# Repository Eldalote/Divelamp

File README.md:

# Divelamp
Designing my own dive lamp

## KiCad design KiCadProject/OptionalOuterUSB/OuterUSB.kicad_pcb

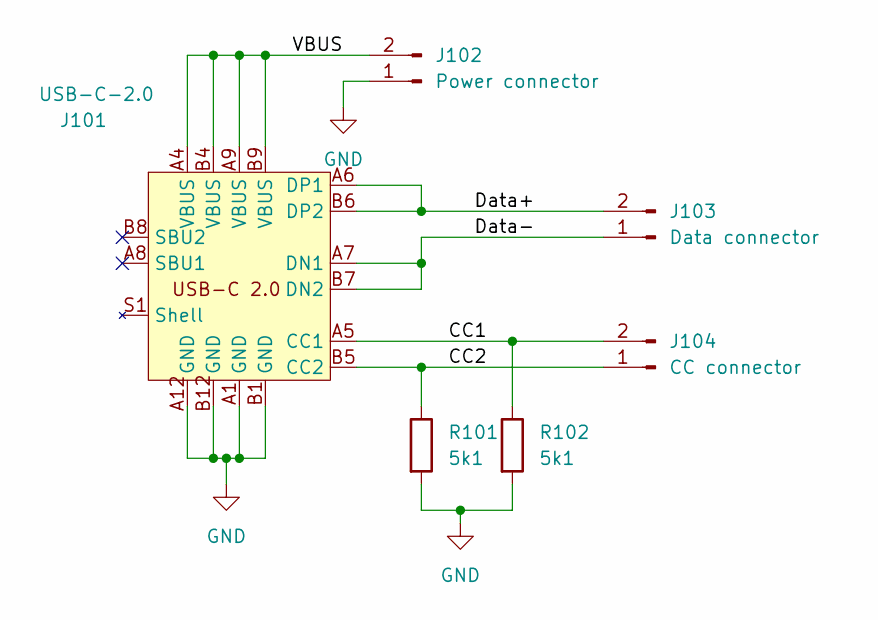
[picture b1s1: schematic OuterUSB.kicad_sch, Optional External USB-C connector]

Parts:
J101: USB-C-2.0; MOLEX_2130830005
J102: Power connector; PinHeader_1x02_P2.54mm_Vertical
J103: Data connector; PinHeader_1x02_P1.27mm_Vertical
J104: CC connector; PinHeader_1x02_P1.27mm_Vertical
R101, R102: 5k1; R_0402_1005Metric

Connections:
/CC1: J101.A5 (CC1), J104.2, R102.1
/CC2: J101.B5 (CC2), J104.1, R101.1
/Data+: J101.A6 (DP1), J101.B6 (DP2), J103.2
/Data-: J101.A7 (DN1), J101.B7 (DN2), J103.1
/VBUS: J101.A4 (VBUS), J101.A9 (VBUS), J101.B4 (VBUS), J101.B9 (VBUS), J102.2
GND: J101.A1 (GND), J101.A12 (GND), J101.B1 (GND), J101.B12 (GND), J102.1, R101.2, R102.2

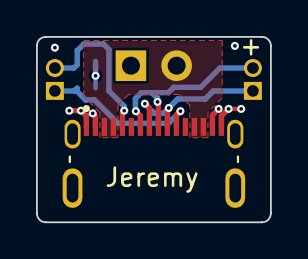
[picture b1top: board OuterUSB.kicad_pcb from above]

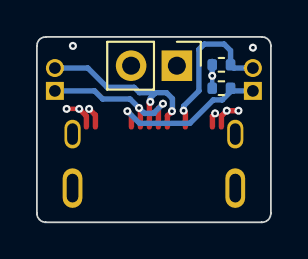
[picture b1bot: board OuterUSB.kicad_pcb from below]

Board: 4 copper layers, 13.0 x 10.3 mm, 6 parts (4 on the bottom side), 6 nets.

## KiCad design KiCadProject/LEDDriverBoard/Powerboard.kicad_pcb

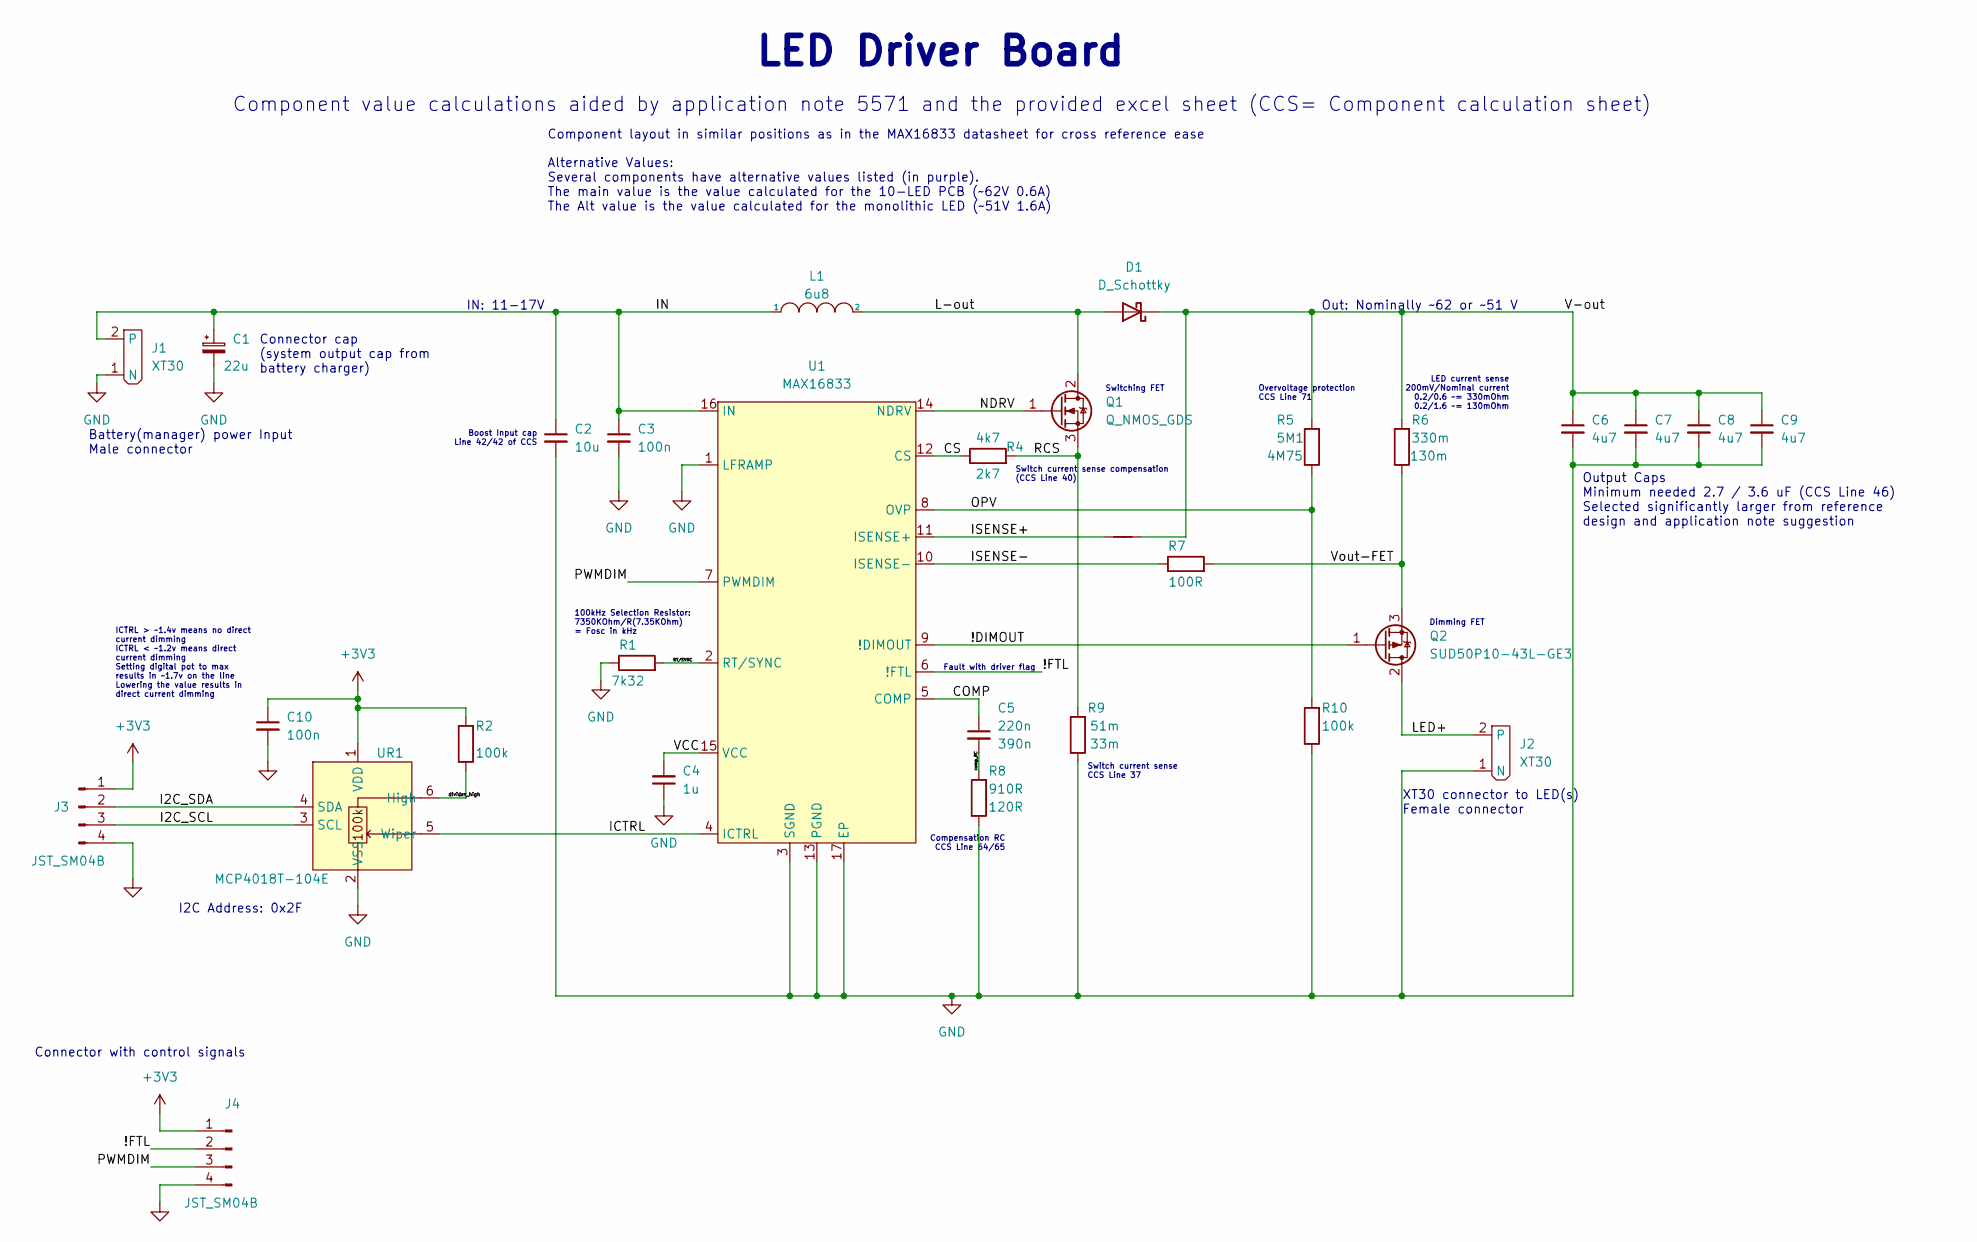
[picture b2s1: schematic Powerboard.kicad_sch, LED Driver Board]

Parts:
C1: 22u; CP_Elec_5x5.3
C2: 10u; C_1206_3216Metric
C3: 100n; C_0603_1608Metric
C4: 1u; C_0402_1005Metric
C5: 220n; C_0603_1608Metric
C6, C7, C8, C9: 4u7; C_1206_3216Metric
C10: 100n; C_0402_1005Metric
D1: D_Schottky; D_PowerDI-5
J1: XT30
J2: XT30; XT30_Female
J3, J4: JST_SM04B; JST_SH_SM04B-SRSS-TB_1x04-1MP_P1.00mm_Horizontal
L1: 6u8; SRP-1265C
NT1: NetTie_2; NetTie-2_SMD_Pad0.5mm
Q1: Q_NMOS_GDS; TO-252-2
Q2: SUD50P10-43L-GE3; TO-252-2
R1: 7k32; R_0402_1005Metric
R2, R10: 100k; R_0402_1005Metric
R4: 4k7; R_0402_1005Metric
R5: 5M1; R_0603_1608Metric
R6: 330m; R_1206_3216Metric
R7: 100R; R_0805_2012Metric
R8: 910R; R_0402_1005Metric
R9: 51m; R_1206_3216Metric
U1: MAX16833; HTSSOP-16-1EP_4.4x5mm_P0.65mm_EP3.4x5mm_Mask2.46x2.31mm_The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
UR1: MCP4018T-104E; SOT-363_SC-70-6

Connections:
+3V3: C10.1, J3.1, J4.1, R2.2, UR1.1 (VDD)
/!DIMOUT: Q2.1 (G), U1.9 (!DIMOUT)
/!FTL: J4.2, U1.6 (!FTL)
/COMP: C5.1, U1.5 (COMP)
/CS: R4.1, U1.12 (CS)
/I2C_SCL: J3.3, UR1.3 (SCL)
/I2C_SDA: J3.2, UR1.4 (SDA)
/ICTRL: U1.4 (ICTRL), UR1.5 (Wiper)
/IN: C1.1, C2.1, C3.1, J1.2, L1.1, U1.16 (IN)
/ISENSE+: NT1.1, U1.11 (ISENSE+)
/ISENSE-: R7.1, U1.10 (ISENSE-)
/L-out: D1.2 (A), L1.2, Q1.2 (D)
/LED+: J2.2, Q2.2 (D)
/NDRV: Q1.1 (G), U1.14 (NDRV)
/OPV: R5.1, R10.2, U1.8 (OVP)
/PWMDIM: J4.3, U1.7 (PWMDIM)
/RCS: Q1.3 (S), R4.2, R9.2
/RT/SYNC: R1.2, U1.2 (RT/SYNC)
/V-out: C6.1, C7.1, C8.1, C9.1, D1.1 (K), NT1.2, R5.2, R6.2
/VCC: C4.2, U1.15 (VCC)
/Vout-FET: Q2.3 (S), R6.1, R7.2
/comp_RC: C5.2, R8.2
/divider_high: R2.1, UR1.6 (High)
GND: C1.2, C2.2, C3.2, C4.1, C6.2, C7.2, C8.2, C9.2, C10.2, J1.1 (N), J2.1 (N), J3.4, J4.4, R1.1, R8.1, R9.1, R10.1, U1.1 (LFRAMP), U1.3 (SGND), U1.13 (PGND), U1.17 (EP), UR1.2 (VSS)

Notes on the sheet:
Switch current sense CCS Line 37
Connector cap (system output cap from battery charger)
ICTRL > ~1.4v means no direct current dimming ICTRL < ~1.2v means direct current dimming Setting digital pot to max results in ~1.7v on the line Lowering the value results in direct current dimming
LED current sense 200mV/Nominal current 0.2/0.6 ~= 330mOhm 0.2/1.6 ~= 130mOhm
Compensation RC CCS Line 64/65
Dimming FET
Fault with driver flag
XT30 connector to LED(s) Female connector
Switch current sense compensation (CCS Line 40)
Out: Nominally ~62 or ~51 V
Connector with control signals
I2C Address: 0x2F
Switching FET
Overvoltage protection CCS Line 71
Output Caps Minimum needed 2.7 / 3.6 uF (CCS Line 46) Selected significantly larger from reference design and application note suggestion
LED Driver Board
Component value calculations aided by application note 5571 and the provided excel sheet (CCS= Component calculation sheet)
IN: 11-17V
Alternative Values: Several components have alternative values listed (in purple). The main value is the value calculated for the 10-LED PCB (~62V 0.6A) The Alt value is the value calculated for the monolithic LED (~51V 1.6A)
Boost Input cap Line 42/42 of CCS
Component layout in similar positions as in the MAX16833 datasheet for cross reference ease
100kHz Selection Resistor: 7350KOhm/R(7.35KOhm) = Fosc in kHz
Battery(manager) power Input Male connector

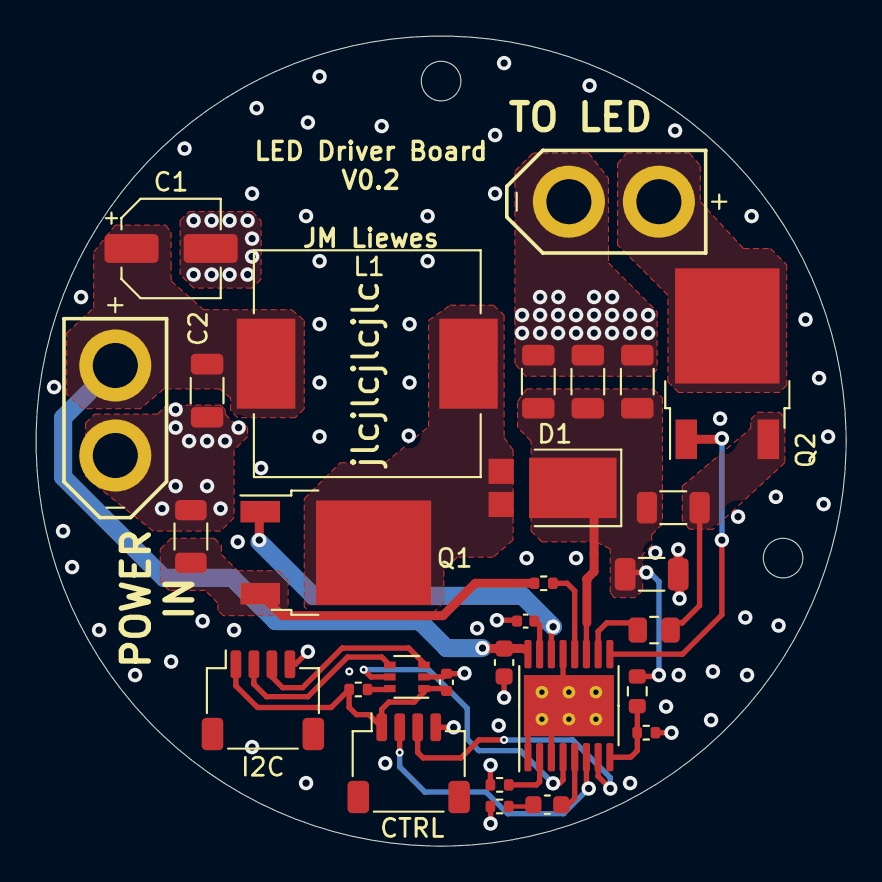
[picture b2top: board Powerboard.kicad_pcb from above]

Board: 4 copper layers, 45.0 x 45.0 mm, 30 parts (0 on the bottom side), 24 nets.

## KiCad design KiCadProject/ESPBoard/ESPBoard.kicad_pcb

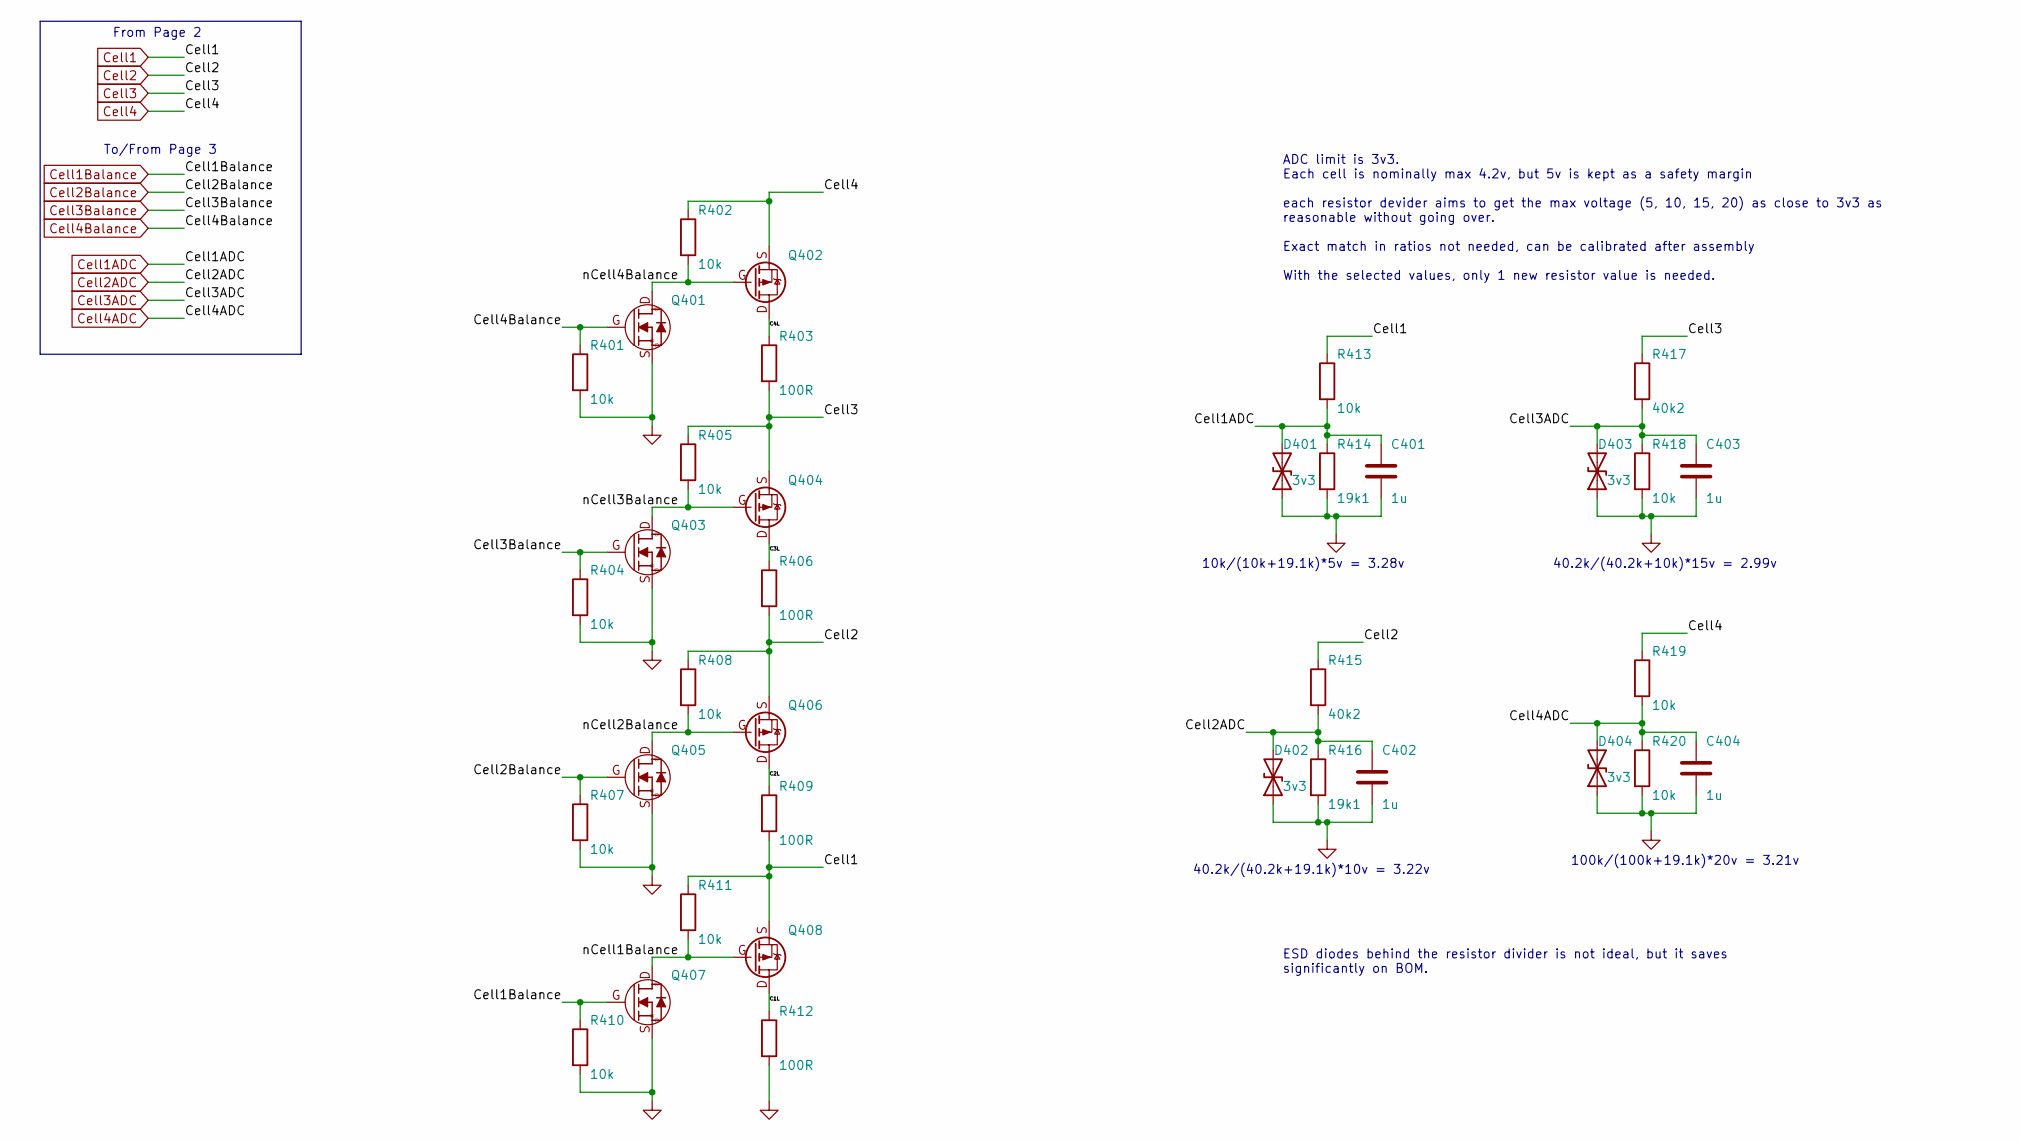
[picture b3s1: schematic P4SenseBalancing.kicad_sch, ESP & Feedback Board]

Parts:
C401, C402, C403, C404: 1u; C_0603_1608Metric
D401, D402, D403, D404: 3v3; D_SOD-523
Q401, Q403, Q405, Q407: NFET_Gatenames; SC-89(GSD)
Q402, Q404, Q406, Q408: PMOS_Gatenames; SOT-723(GSD)
R401, R402, R404, R405, R407, R408, R410, R411, R413, R418, R419, R420: 10k; R_0402_1005Metric
R403, R406, R409, R412: 100R; R_0805_2012Metric
R414, R416: 19k1; R_0402_1005Metric
R415, R417: 40k2; R_0402_1005Metric

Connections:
/P4 Batsense-Balancing/C1L: Q408.D, R412.1
/P4 Batsense-Balancing/C2L: Q406.D, R409.1
/P4 Batsense-Balancing/C3L: Q404.D, R406.1
/P4 Batsense-Balancing/C4L: Q402.D, R403.1
/P4 Batsense-Balancing/nCell1Balance: Q407.D, Q408.G, R411.2
/P4 Batsense-Balancing/nCell2Balance: Q405.D, Q406.G, R408.2
/P4 Batsense-Balancing/nCell3Balance: Q403.D, Q404.G, R405.2
/P4 Batsense-Balancing/nCell4Balance: Q401.D, Q402.G, R402.2
Cell1: Q408.S, R409.2, R411.1, R413.1; also elsewhere on the board
Cell1ADC: C401.1, D401.2 (A2), R413.2, R414.1; also elsewhere on the board
Cell1Balance: Q407.G, R410.1; also elsewhere on the board
Cell2: Q406.S, R406.2, R408.1, R415.1; also elsewhere on the board
Cell2ADC: C402.1, D402.2 (A2), R415.2, R416.1; also elsewhere on the board
Cell2Balance: Q405.G, R407.1; also elsewhere on the board
Cell3: Q404.S, R403.2, R405.1, R417.1; also elsewhere on the board
Cell3ADC: C403.1, D403.2 (A2), R417.2, R418.1; also elsewhere on the board
Cell3Balance: Q403.G, R404.1; also elsewhere on the board
Cell4: Q402.S, R402.1, R419.1; also elsewhere on the board
Cell4ADC: C404.1, D404.2 (A2), R419.2, R420.1; also elsewhere on the board
Cell4Balance: Q401.G, R401.1; also elsewhere on the board
GND: C401.2, C402.2, C403.2, C404.2, D401.1 (A1), D402.1 (A1), D403.1 (A1), D404.1 (A1), Q401.S, Q403.S, Q405.S, Q407.S, R401.2, R404.2, R407.2, R410.2, R412.2, R414.2, R416.2, R418.2, R420.2; also elsewhere on the board

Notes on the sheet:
10k/(10k+19.1k)*5v = 3.28v
40.2k/(40.2k+10k)*15v = 2.99v
40.2k/(40.2k+19.1k)*10v = 3.22v
100k/(100k+19.1k)*20v = 3.21v
ADC limit is 3v3. Each cell is nominally max 4.2v, but 5v is kept as a safety margin each resistor devider aims to get the max voltage (5, 10, 15, 20) as close to 3v3 as reasonable without going over. Exact match in ratios not needed, can be calibrated after assembly With the selected values, only 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
From Page 2
ESD diodes behind the resistor divider is not ideal, but it saves significantly on BOM.
To/From Page 3

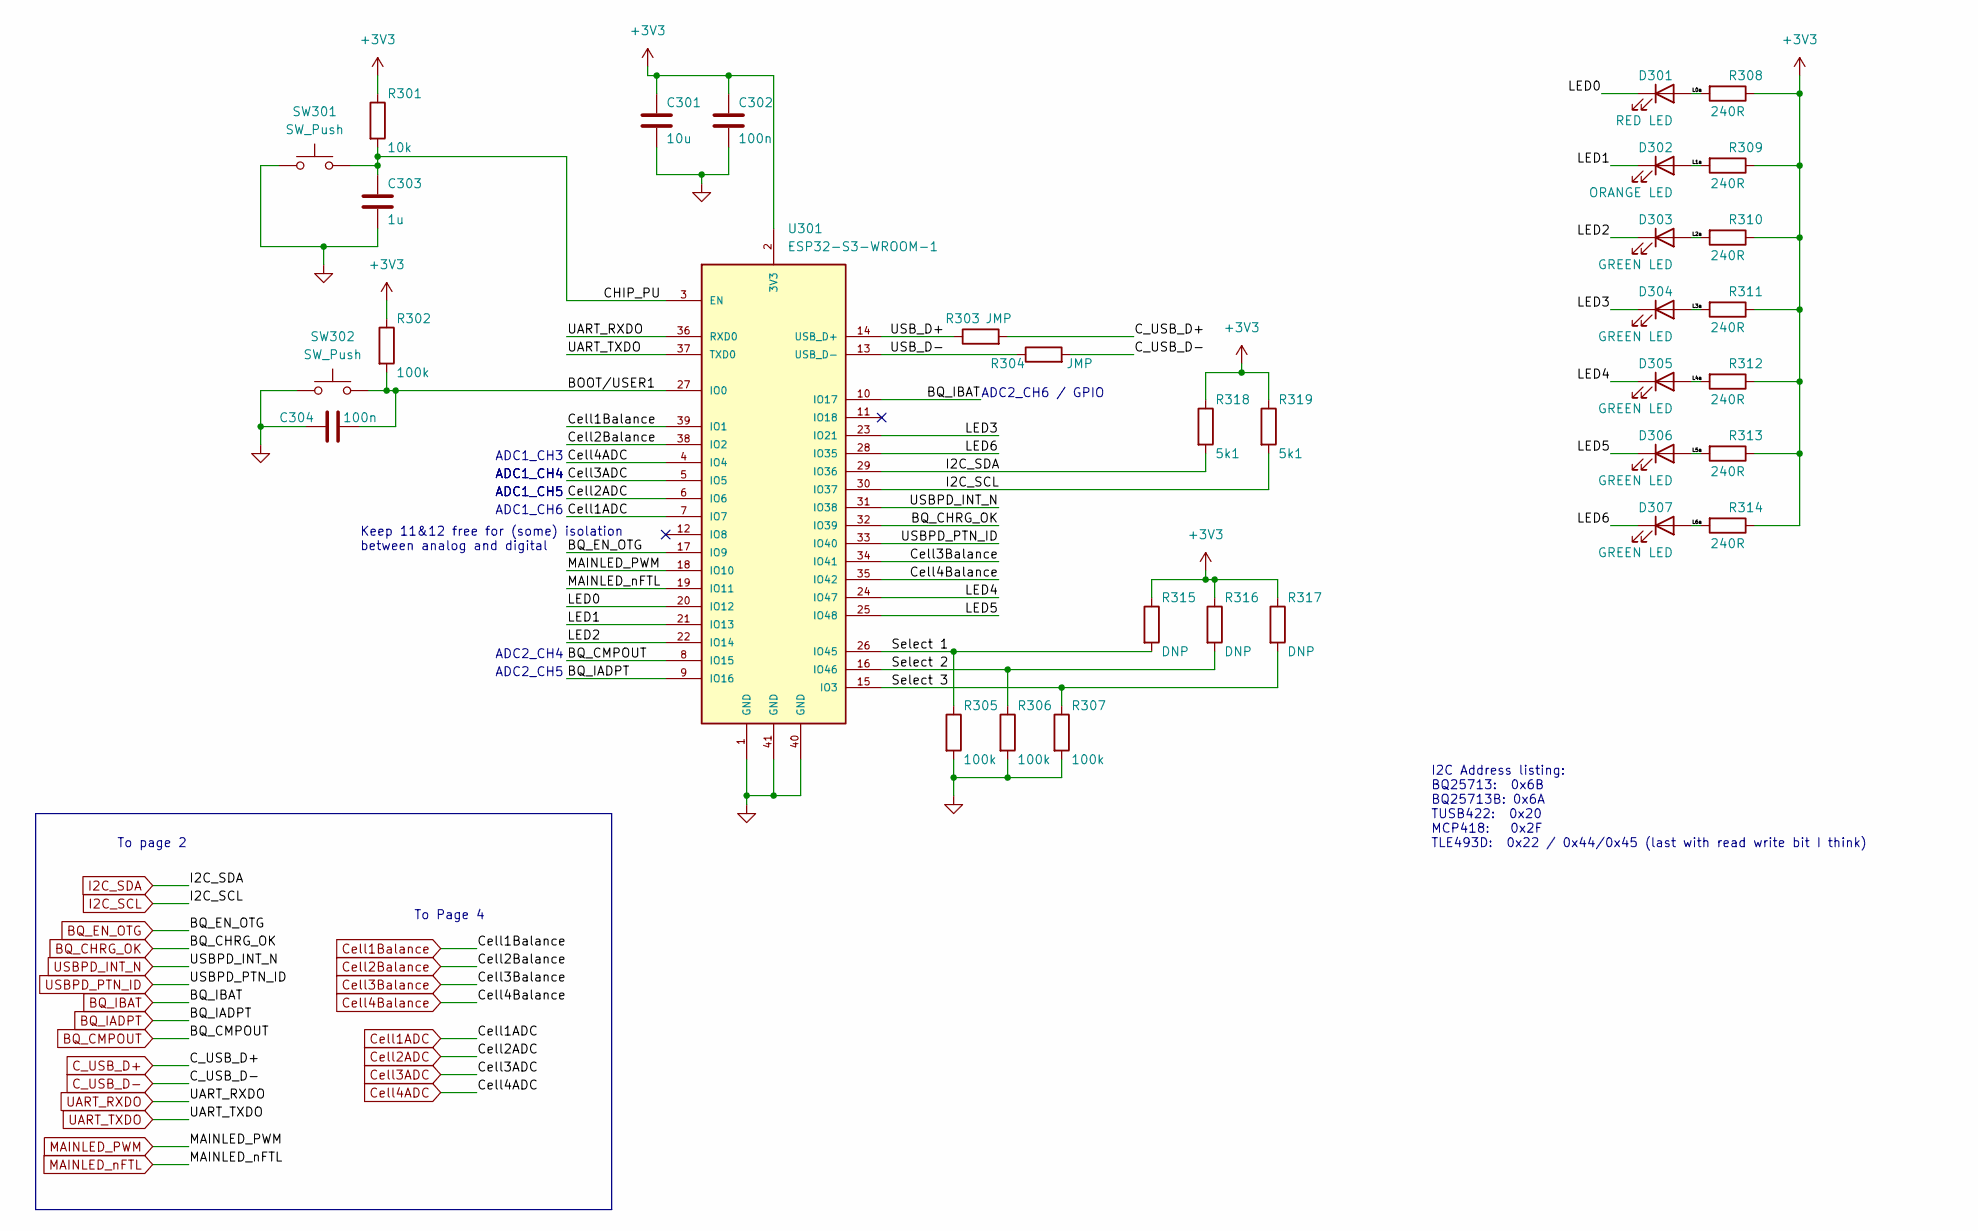
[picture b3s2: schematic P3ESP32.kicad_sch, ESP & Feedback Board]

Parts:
C301: 10u; C_0805_2012Metric
C302, C304: 100n; C_0402_1005Metric
C303: 1u; C_0603_1608Metric
D301: RED LED; LED_0805_2012Metric
D302: ORANGE LED; LED_0805_2012Metric
D303, D304, D305, D306, D307: GREEN LED; LED_0805_2012Metric
R301: 10k; R_0402_1005Metric
R302, R305, R306, R307: 100k; R_0402_1005Metric
R303, R304: JMP; R_0402_1005Metric
R308, R309, R310, R311, R312, R313, R314: 240R; R_0402_1005Metric
R315, R316, R317: DNP; R_0402_1005Metric
R318, R319: 5k1; R_0402_1005Metric
SW301, SW302: SW_Push; SW_Push_1P1T_NO_6x6mm_H9.5mm
U301: ESP32-S3-WROOM-1; XCVR_ESP32-S3-WROOM-1

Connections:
+3V3: C301.1, C302.1, R301.1, R302.1, R308.1, R309.1, R310.1, R311.1, R312.1, R313.1, R314.1, R315.1, R316.1, R317.1, R318.1, R319.1, U301.2 (3V3); also elsewhere on the board
/P3 ESP32/BOOT/USER1: C304.2, R302.2, SW302.2, U301.27 (IO0)
/P3 ESP32/CHIP_PU: C303.1, R301.2, SW301.2, U301.3 (EN)
/P3 ESP32/L0a: D301.2 (A), R308.2
/P3 ESP32/L1a: D302.2 (A), R309.2
/P3 ESP32/L2a: D303.2 (A), R310.2
/P3 ESP32/L3a: D304.2 (A), R311.2
/P3 ESP32/L4a: D305.2 (A), R312.2
/P3 ESP32/L5a: D306.2 (A), R313.2
/P3 ESP32/L6a: D307.2 (A), R314.2
/P3 ESP32/LED0: D301.1 (K), U301.20 (IO12)
/P3 ESP32/LED1: D302.1 (K), U301.21 (IO13)
/P3 ESP32/LED2: D303.1 (K), U301.22 (IO14)
/P3 ESP32/LED3: D304.1 (K), U301.23 (IO21)
/P3 ESP32/LED4: D305.1 (K), U301.24 (IO47)
/P3 ESP32/LED5: D306.1 (K), U301.25 (IO48)
/P3 ESP32/LED6: D307.1 (K), U301.28 (IO35)
/P3 ESP32/Select 1: R305.1, R315.2, U301.26 (IO45)
/P3 ESP32/Select 2: R306.1, R316.2, U301.16 (IO46)
/P3 ESP32/Select 3: R307.1, R317.2, U301.15 (IO3)
/P3 ESP32/USB_D+: R303.1, U301.14 (USB_D+)
/P3 ESP32/USB_D-: R304.1, U301.13 (USB_D-)
BQ_CHRG_OK: U301.32 (IO39); also elsewhere on the board
BQ_CMPOUT: U301.8 (IO15); also elsewhere on the board
BQ_EN_OTG: U301.17 (IO9); also elsewhere on the board
BQ_IADPT: U301.9 (IO16); also elsewhere on the board
BQ_IBAT: U301.10 (IO17); also elsewhere on the board
C_USB_D+: R303.2; also elsewhere on the board
C_USB_D-: R304.2; also elsewhere on the board
Cell1ADC: U301.7 (IO7); also elsewhere on the board
Cell1Balance: U301.39 (IO1); also elsewhere on the board
Cell2ADC: U301.6 (IO6); also elsewhere on the board
Cell2Balance: U301.38 (IO2); also elsewhere on the board
Cell3ADC: U301.5 (IO5); also elsewhere on the board
Cell3Balance: U301.34 (IO41); also elsewhere on the board
Cell4ADC: U301.4 (IO4); also elsewhere on the board
Cell4Balance: U301.35 (IO42); also elsewhere on the board
GND: C301.2, C302.2, C303.2, C304.1, R305.2, R306.2, R307.2, SW301.1, SW302.1, U301.1 (GND), U301.40 (GND), U301.41 (GND); also elsewhere on the board
I2C_SCL: R319.2, U301.30 (IO37); also elsewhere on the board
I2C_SDA: R318.2, U301.29 (IO36); also elsewhere on the board
MAINLED_PWM: U301.18 (IO10); also elsewhere on the board
MAINLED_nFTL: U301.19 (IO11); also elsewhere on the board
UART_RXDO: U301.36 (RXD0); also elsewhere on the board
UART_TXDO: U301.37 (TXD0); also elsewhere on the board
USBPD_INT_N: U301.31 (IO38); also elsewhere on the board
USBPD_PTN_ID: U301.33 (IO40); also elsewhere on the board

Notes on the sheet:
ADC1_CH4
To page 2
I2C Address listing: BQ25713: 0x6B BQ25713B: 0x6A TUSB422: 0x20 MCP418: 0x2F TLE493D: 0x22 / 0x44/0x45 (last with read write bit I think)
To Page 4
ADC1_CH5
ADC1_CH3
ADC2_CH4
ADC2_CH5
Keep 11&12 free for (some) isolation between analog and digital
ADC2_CH6 / GPIO
ADC1_CH6

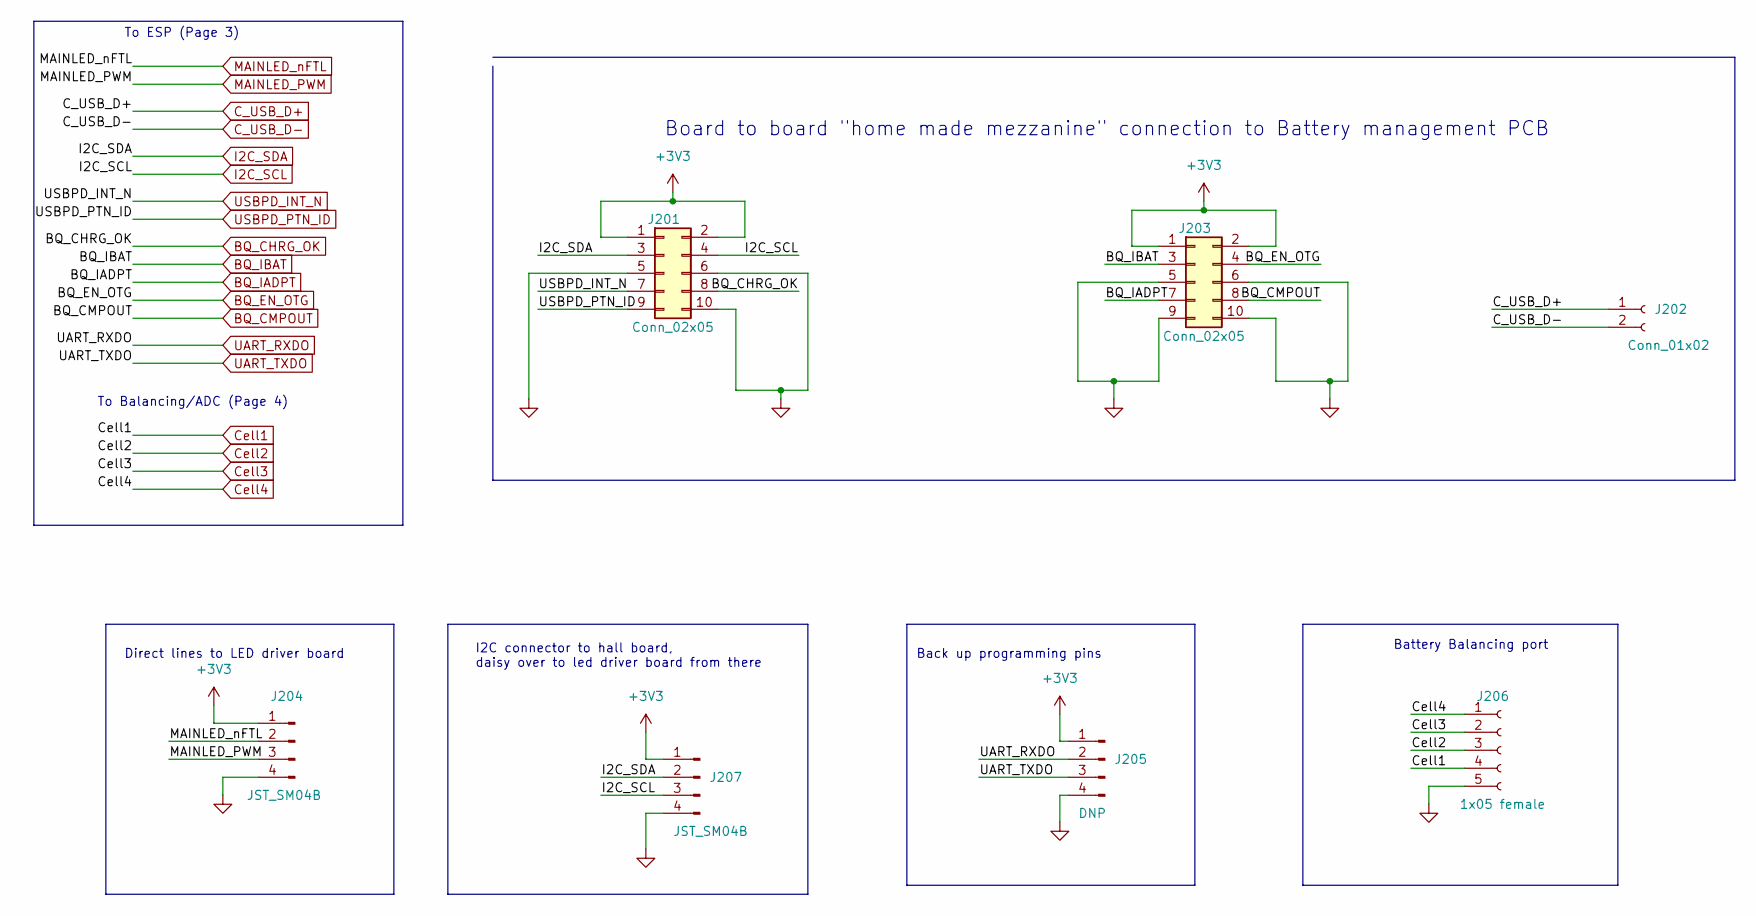
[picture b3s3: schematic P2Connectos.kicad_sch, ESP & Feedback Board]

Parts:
J201, J203: Conn_02x05; PinSocket_2x05_P1.27mm_Vertical_SMD
J202: Conn_01x02; PinSocket_1x02_P1.27mm_Vertical_SMD_Pin1Left
J204, J207: JST_SM04B; JST_SH_SM04B-SRSS-TB_1x04-1MP_P1.00mm_Horizontal
J205: DNP; PinHeader_2x02_P1.27mm_Vertical_SMD
J206: 1x05 female; PinSocket_1x05_P1.27mm_Vertical_SMD_Pin1Left

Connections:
+3V3: J201.1, J201.2, J203.1, J203.2, J204.1, J205.1, J207.1; also elsewhere on the board
BQ_CHRG_OK: J201.8; also elsewhere on the board
BQ_CMPOUT: J203.8; also elsewhere on the board
BQ_EN_OTG: J203.4; also elsewhere on the board
BQ_IADPT: J203.7; also elsewhere on the board
BQ_IBAT: J203.3; also elsewhere on the board
C_USB_D+: J202.1; also elsewhere on the board
C_USB_D-: J202.2; also elsewhere on the board
Cell1: J206.4; also elsewhere on the board
Cell2: J206.3; also elsewhere on the board
Cell3: J206.2; also elsewhere on the board
Cell4: J206.1; also elsewhere on the board
GND: J201.5, J201.6, J201.10, J203.5, J203.6, J203.9, J203.10, J204.4, J205.4, J206.5, J207.4; also elsewhere on the board
I2C_SCL: J201.4, J207.3; also elsewhere on the board
I2C_SDA: J201.3, J207.2; also elsewhere on the board
MAINLED_PWM: J204.3; also elsewhere on the board
MAINLED_nFTL: J204.2; also elsewhere on the board
UART_RXDO: J205.2; also elsewhere on the board
UART_TXDO: J205.3; also elsewhere on the board
USBPD_INT_N: J201.7; also elsewhere on the board
USBPD_PTN_ID: J201.9; also elsewhere on the board

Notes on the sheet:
To ESP (Page 3)
Back up programming pins
To Balancing/ADC (Page 4)
Board to board "home made mezzanine" connection to Battery management PCB
Battery Balancing port
I2C connector to hall board, daisy over to led driver board from there
Direct lines to LED driver board

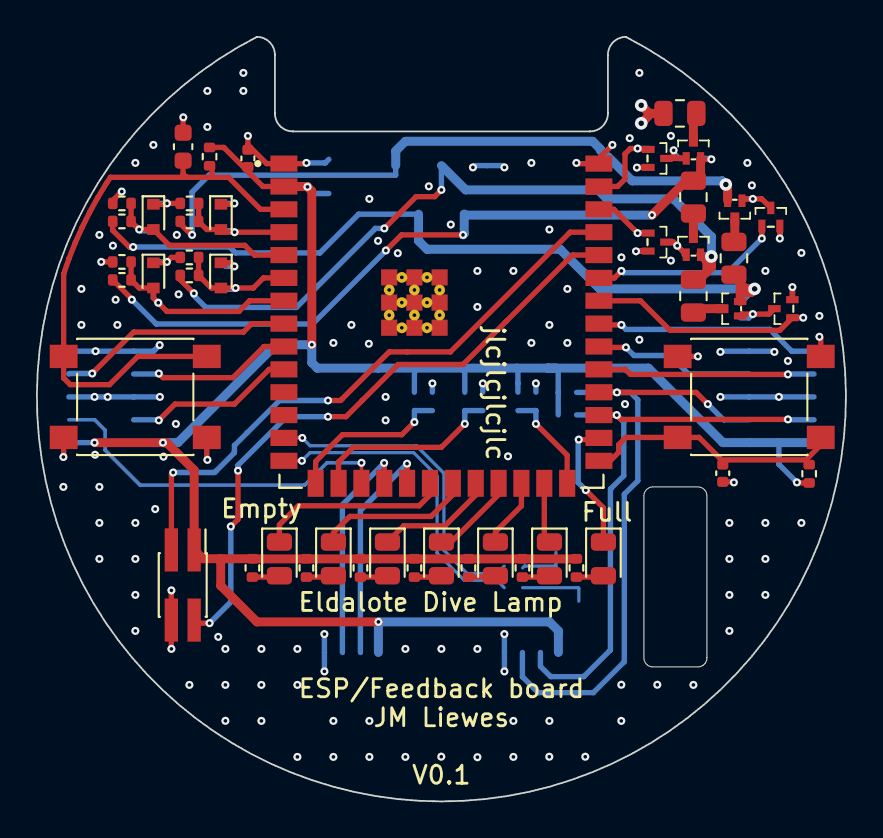
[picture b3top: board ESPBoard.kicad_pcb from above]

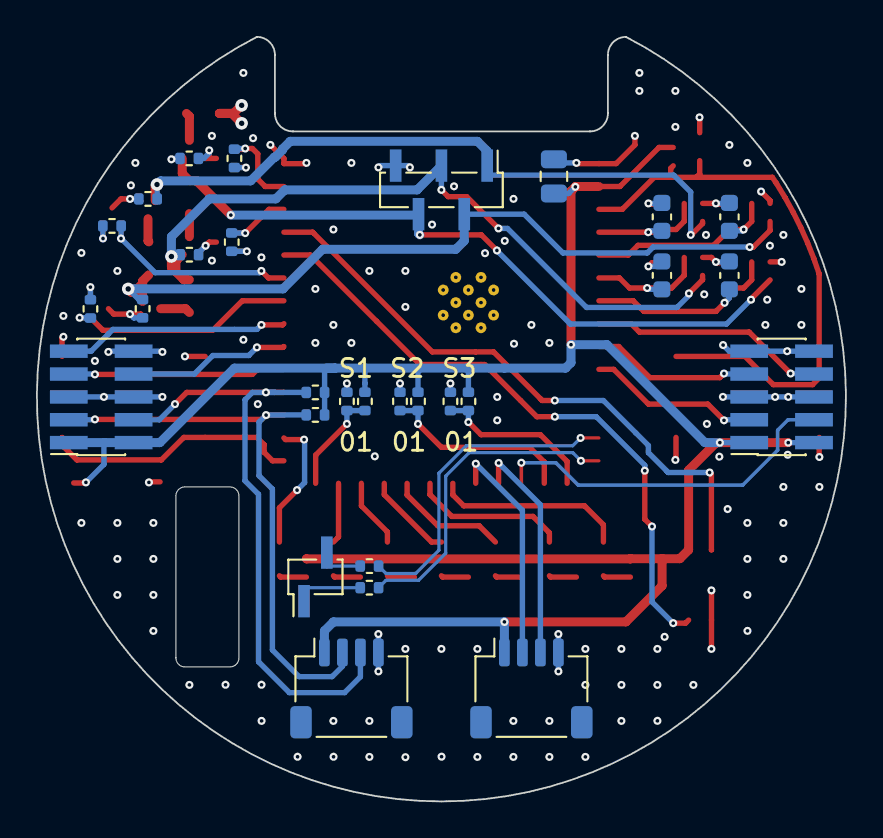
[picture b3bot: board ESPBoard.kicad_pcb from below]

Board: 4 copper layers, 44.9 x 42.5 mm, 76 parts (29 on the bottom side), 58 nets.
